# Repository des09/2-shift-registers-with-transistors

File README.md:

# 2-shift-registers-with-transistors

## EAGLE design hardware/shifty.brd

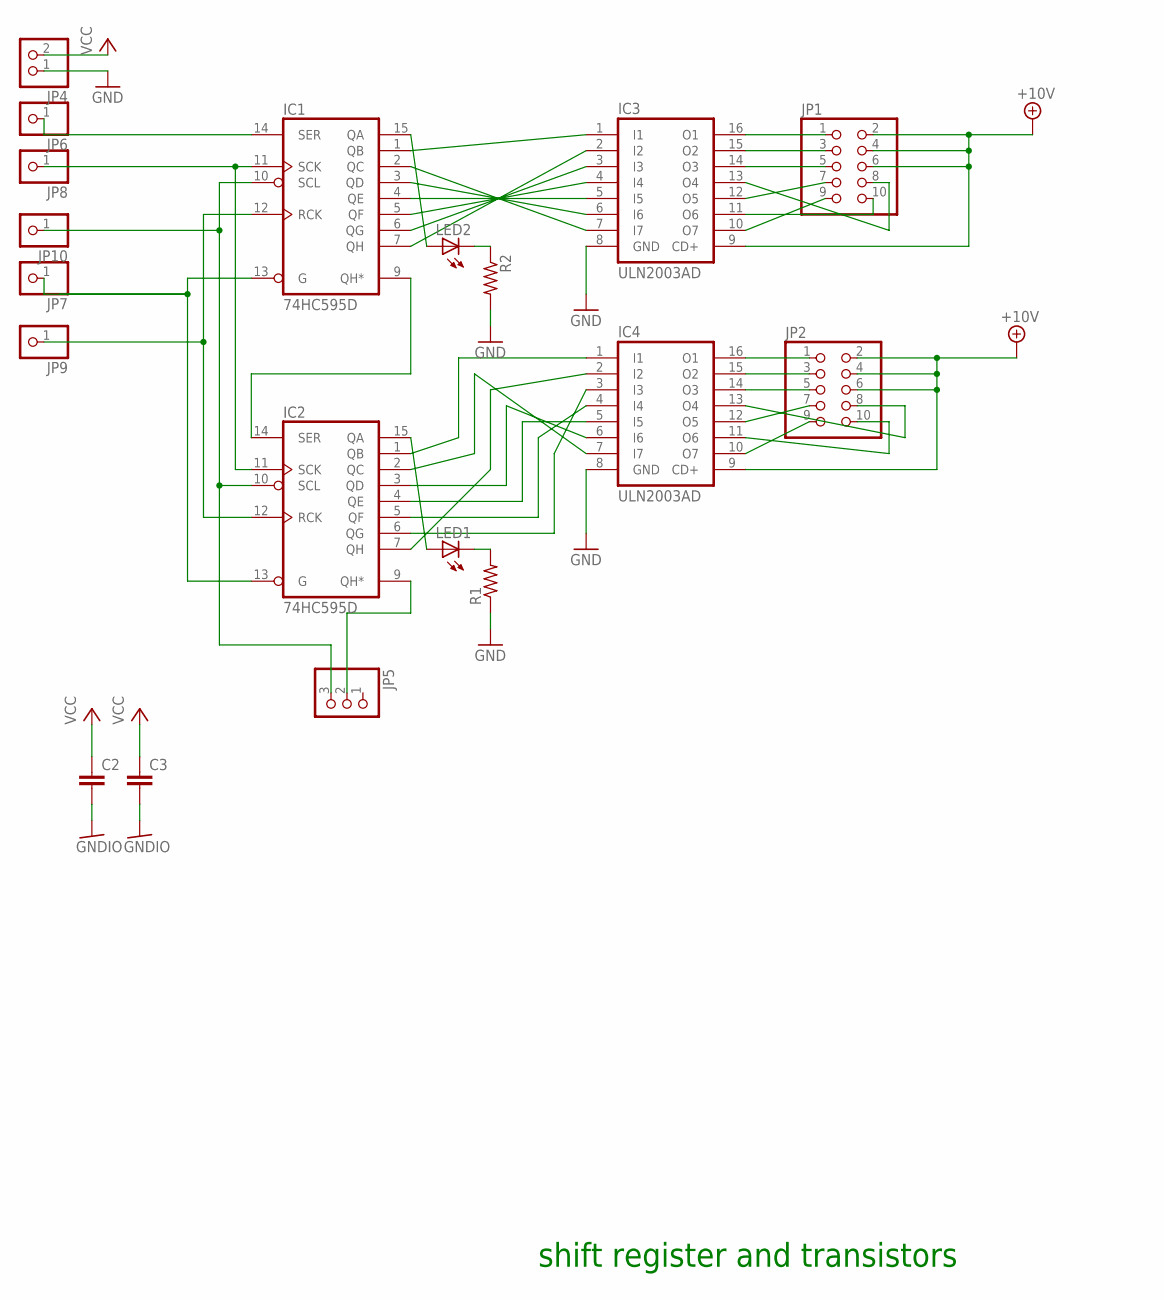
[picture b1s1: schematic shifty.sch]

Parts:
C2, C3: C-EUC0805; C0805
IC1, IC2: 74HC595D; SO16
IC3, IC4: ULN2003AD; SO16
JP1, JP2: PINHD-2X5; 2X05
JP4: PINHD-1X2; 1X02
JP5: PINHD-1X3; 1X03
JP6, JP7, JP8, JP9, JP10: PINHD-1X1; 1X01
LED1, LED2: LEDCHIP-LED0603; CHIP-LED0603
R1, R2: R-US_R0603; R0603

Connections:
+10V: IC3.9 (CD+), IC4.9 (CD+), JP1.2, JP1.4, JP1.6, JP2.2, JP2.4, JP2.6
GND: IC1.8 (GND), IC2.8 (GND), IC3.8 (GND), IC4.8 (GND), JP4.1, R1.1, R2.2
GNDIO: C2.2, C3.2
unnamed: IC1.1 (QB), IC3.1 (I1)
unnamed: IC1.7 (QH), IC3.2 (I2)
unnamed: IC1.2 (QC), IC3.7 (I7)
unnamed: IC1.3 (QD), IC3.6 (I6)
unnamed: IC1.4 (QE), IC3.5 (I5)
unnamed: IC1.5 (QF), IC3.4 (I4)
unnamed: IC1.6 (QG), IC3.3 (I3)
unnamed: IC1.11 (SCK), IC2.11 (SCK), JP8.1
unnamed: IC2.1 (QB), IC4.1 (I1)
unnamed: IC2.2 (QC), IC4.7 (I7)
unnamed: IC2.7 (QH), IC4.2 (I2)
unnamed: IC2.3 (QD), IC4.6 (I6)
unnamed: IC2.4 (QE), IC4.5 (I5)
unnamed: IC2.5 (QF), IC4.4 (I4)
unnamed: IC2.6 (QG), IC4.3 (I3)
unnamed: IC1.14 (SER), JP6.1
unnamed: IC2.15 (QA), LED1.A
unnamed: IC1.10 (SCL), IC2.10 (SCL), JP5.3, JP10.1
unnamed: IC1.9 (QH*), IC2.14 (SER)
unnamed: IC1.12 (RCK), IC2.12 (RCK), JP9.1
unnamed: IC3.16 (O1), JP1.1
unnamed: IC3.15 (O2), JP1.3
unnamed: IC3.14 (O3), JP1.5
unnamed: IC3.12 (O5), JP1.7
unnamed: IC3.10 (O7), JP1.9
unnamed: IC3.11 (O6), JP1.10
unnamed: IC3.13 (O4), JP1.8
unnamed: LED1.C, R1.2
unnamed: IC2.9 (QH*), JP5.2
unnamed: IC4.16 (O1), JP2.1
unnamed: IC4.15 (O2), JP2.3
unnamed: IC4.14 (O3), JP2.5
unnamed: IC4.12 (O5), JP2.7
unnamed: IC4.10 (O7), JP2.9
unnamed: IC4.13 (O4), JP2.8
unnamed: IC4.11 (O6), JP2.10
unnamed: LED2.C, R2.1
unnamed: IC1.15 (QA), LED2.A
unnamed: IC1.13 (G), IC2.13 (G), JP7.1
VCC: C2.1, C3.1, IC1.16 (VCC), IC2.16 (VCC), JP4.2

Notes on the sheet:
shift register and transistors

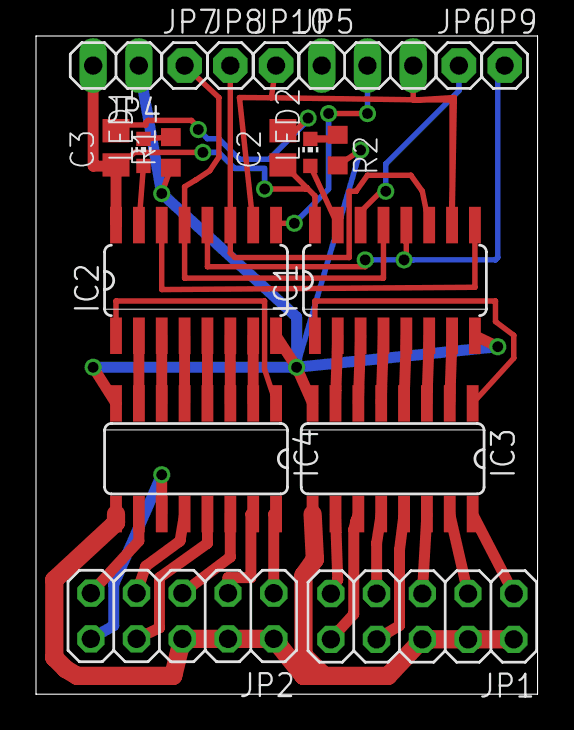
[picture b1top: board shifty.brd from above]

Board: 2 copper layers, 27.9 x 36.6 mm, 19 parts (0 on the bottom side), 43 nets.

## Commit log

2015-03-12 ready to start routing?
2015-03-14 started routing
2015-03-15 Board lay-out done
